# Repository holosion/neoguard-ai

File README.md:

# NeoGuard

NeoGuard is an offline-aware neonatal monitoring prototype for organizing clinical staff, patients, monitoring devices, vital-sign readings, alerts, and historical trends. It combines a React dashboard, a FastAPI service, and PostgreSQL. A separate experimental AI package trains a research-only warning model.

> **Project status:** This is a development and research prototype, not a clinically validated medical device or a production-ready care system. The AI model is trained on simulated data and is not clinically validated. Thresholds are provisional and require qualified clinical review before any care use. Current ESP32-S3 firmware uses the tested ST7789 screen, sensors, DS1302 clock, RGB/buzzer and SD logging. Wi-Fi provisioning and queued HTTPS synchronization are enabled after offline integration checks. See the firmware's current validation report for the actual hardware checks and limits.

## What the project does

- Provides sign-in for administrators, clinicians, and nurses, with role-aware and clinic-scoped access.
- Lets authorized staff manage patients, devices, monitoring sessions, alerts, and configured vital-sign thresholds.
- Accepts authenticated device sync batches and stores time-stamped readings and device telemetry in PostgreSQL.
- Uses stored readings to serve patient history and trend charts; dashboard values come from the API rather than a frontend sample-data mode.
- Tracks data freshness so staff can distinguish current readings from stale or missing data.
- Supports offline-safe sync: device event identifiers make retries idempotent, and readings retain their original session assignment.
- Optionally stores experimental model score snapshots separately from measured readings and deterministic threshold alerts.
- Keeps imported archive/training data in separate review tables instead of creating live patients or clinical readings.

## Repository map

```text
NeoGuard/
├── README.md                    # Project overview and setup (this file)
├── start-local.ps1              # Optional Windows launcher
├── LOCAL-RUN.md                 # Short local startup reference
├── backend/
│   ├── app/                     # FastAPI routes, auth, models, schemas, services
│   ├── migrations/              # Alembic database schema history
│   ├── scripts/                 # Admin bootstrap, smoke check, archive import
│   ├── tests/                   # API and PostgreSQL integration tests
│   ├── .env.example             # Backend configuration template
│   └── requirements*.txt        # Python dependencies
├── Frontend/
│   ├── src/                     # React pages, API clients, charts and components
│   ├── package.json             # Frontend scripts and dependencies
│   └── .env.example             # Frontend API configuration template
├── ai/
│   ├── train.py                 # Synthetic prototype training pipeline
│   ├── artifacts/               # Saved model artifact used by the API
│   ├── reports/                  # Training and archive audit reports
│   └── tests/                    # AI feature/model tests
├── akena firmware/akena_firmware/ # Current ESP32-S3 ST7789 firmware and setup guide
└── firmware/tests/              # Host-side measurement checks
```

## System architecture and data flow

```mermaid
flowchart LR
    Staff[Admin / clinician / nurse] --> UI[React dashboard]
    UI -->|REST requests, /api/v1| API[FastAPI]
    Device[Monitoring device] -->|Device-authenticated sync batch| API
    API -->|SQLAlchemy| DB[(PostgreSQL)]
    API -->|Patient history / overview / alerts| UI
    API -->|Optional experimental inference| Model[AI model artifact]
    API -->|Persist score snapshot separately| DB
```

The frontend calls the backend through `/api/v1`. In local development, Vite proxies API requests to FastAPI. Devices submit readings to the device sync endpoint using a provisioned device credential. The backend validates each item, stores accepted data and generated threshold alerts, and returns per-item results. Patient history and dashboard trends are then queried from PostgreSQL through the API.

The reading's `measured_at` timestamp is distinct from the server's `received_at` timestamp. This preserves when a measurement was taken even if a device uploads it later. A reading is associated with the monitoring session it originally belonged to, including when an offline device uploads after that session has ended. Device event IDs prevent duplicate readings on retry.

There is no frontend mock-data mode. A newly configured database can therefore show empty states until staff create records and a device or an authorized integration sends real readings. The current [device firmware](akena%20firmware/akena_firmware/README.md) reads sensors, drives the ST7789 screen and logs to SD. The network-enabled build reconnects to saved Wi-Fi settings and queues available readings after device/session provisioning. Live estimates carry poor quality until the full stability checks pass; the hosted bench view labels them accordingly.

## Technology

| Area | Current implementation |
|---|---|
| Frontend | React 18, Vite, React Router, Zustand, Recharts, Tailwind CSS |
| Backend | Python, FastAPI, Pydantic Settings, synchronous SQLAlchemy 2 |
| Database | PostgreSQL, managed through Alembic migrations |
| Staff security | JWT bearer access tokens, Argon2 password hashes, role and clinic access checks |
| Device security | Per-device random credential; the API stores a hash and supports credential rotation |
| AI prototype | Scikit-learn synthetic-data training pipeline and a JSON model artifact |
| Local orchestration | FastAPI development startup checks PostgreSQL and launches Vite if it is not already running |

## Start the project locally (Windows)

### Requirements

- Python and Node.js versions compatible with the dependencies in `backend/requirements.txt` and `Frontend/package-lock.json`.
- PostgreSQL installed and available locally, or the bundled local PostgreSQL runtime/data directory if your workspace provides it.
- PowerShell for the commands below and the optional `start-local.ps1` script.

### First-time setup

Run these commands from the repository root in PowerShell:

```powershell
py -m venv backend/.venv
backend/.venv/Scripts/python.exe -m pip install -r backend/requirements-dev.txt

Copy-Item backend/.env.example backend/.env
Copy-Item Frontend/.env.example Frontend/.env

Push-Location Frontend
npm ci
Pop-Location
```

Edit `backend/.env` and set:

- `DATABASE_URL` to the PostgreSQL database and credentials for this project.
- `JWT_SECRET_KEY` to a unique random secret of at least 32 characters. For example, generate one with `py -c "import secrets; print(secrets.token_urlsafe(48))"` and paste the output into the ignored `.env` file.
- `BOOTSTRAP_ADMIN_USERNAME` and `BOOTSTRAP_ADMIN_EMAIL` if you want different initial admin identifiers. Leave `BOOTSTRAP_ADMIN_PASSWORD` empty to enter the password interactively when creating the account.

Never commit `.env` files or share their secrets. The repository's `.gitignore` excludes them.

Create the PostgreSQL role and database if they do not already exist. For example, in a PostgreSQL shell as a database administrator:

```sql
CREATE ROLE neoguard LOGIN PASSWORD 'choose-a-local-password';
CREATE DATABASE neoguard OWNER neoguard;
```

Make `DATABASE_URL` use the same username, password, host, port, and database. Then run the migrations and create the initial admin account:

```powershell
Push-Location backend
.\.venv\Scripts\python.exe -m alembic upgrade head
.\.venv\Scripts\python.exe -m scripts.seed_admin
Pop-Location
```

The seed command creates the administrator and provisional threshold rows. It prompts for an admin password when `BOOTSTRAP_ADMIN_PASSWORD` is blank. It does not print or recover an existing admin password; reset credentials through an authorized operational process.

### Run the whole local application

From the repository root:

```powershell
Push-Location backend
..\.venv\Scripts\python.exe -m uvicorn app.main:app --host 127.0.0.1 --port 8000
```

In development mode, FastAPI checks that the configured PostgreSQL database accepts connections and starts Vite on port `5173` if the expected frontend is not already running. It can start a single installed PostgreSQL Windows service or the bundled local PostgreSQL runtime when available. Schema migrations remain a manual setup/upgrade step. Stop Uvicorn with `Ctrl+C`; it also stops the Vite process that it started. PostgreSQL remains running.

Open:

- Frontend: <http://127.0.0.1:5173>
- API health: <http://127.0.0.1:8000/health>
- Interactive API docs: <http://127.0.0.1:8000/docs> (disabled when `APP_ENV=production`)

Alternatively, run `./start-local.ps1` from the repository root after configuring the environment. The launcher checks dependencies and service readiness and prints the local URLs.

To run the frontend and backend separately, start the backend from `backend/` as above and run `npm run dev` from `Frontend/`. The Vite development server proxies `/api` requests to `http://127.0.0.1:8000`. For a separately hosted frontend, set `VITE_API_BASE_URL` in `Frontend/.env` and configure the deployed origin in backend `CORS_ORIGINS`.

## Main application areas

### Staff dashboard

- **Nurse and clinician views:** ward overview, patient list, patient details, vitals and trend history, active monitoring sessions, alerts, and device information.
- **Administrator views:** system overview, staff accounts and access requests, clinic configuration, device registry/health, sessions, and threshold settings.
- **Authentication:** username or email sign-in, forced password change for temporary credentials, and role-aware protected routes.
- Charts and KPI values are driven by API responses. Empty and stale states are shown when there are no recent readings.

### Backend API

The API prefix is `/api/v1`. The interactive OpenAPI documentation is available at `/docs` in development. Major endpoint groups include:

| Endpoint group | Purpose |
|---|---|
| `/auth` | Staff login, current user, password change, staff provisioning, access requests and administration |
| `/patients` | Patient records, risk profiles, reading history and experimental risk-score availability |
| `/devices` | Device registry, current device session, health/telemetry, secret rotation and device sync |
| `/sessions` | Start, list and stop patient/device monitoring assignments |
| `/alerts` | List/filter alerts and record staff acknowledgment |
| `/admin` | Administrative overview, clinic/user management and device health summaries |
| `/thresholds` | Read and configure rule-based alert thresholds |

Device ingestion uses `POST /api/v1/devices/sync`. Staff endpoints use staff bearer tokens; device sync uses the provisioned device bearer credential. The API validates value ranges, device/session ownership, timestamps, payload size, and duplicate event identifiers. Valid batch items receive accepted, duplicate, or rejected outcomes according to the sync contract.

### Database

PostgreSQL is the source of truth. Alembic migrations define and upgrade the schema; SQLAlchemy models represent its entities. Major data areas include:

- Clinics and staff users, including roles, password lifecycle state, and token versions.
- Patients and clinician-maintained risk profiles.
- Devices, hashed device credentials, registered components, telemetry, and component health.
- Monitoring sessions that link a clinic, patient, and device with database-enforced active-session constraints.
- Time-stamped readings and threshold alerts, including alert acknowledgment records.
- Versioned threshold configuration and audit records.
- Model registry and experimental risk-score snapshots.
- Separate archive import and research dataset tables for review-only data.

Run `alembic upgrade head` from `backend/` whenever pulling a schema migration. Do not use `Base.metadata.create_all()` as a substitute for migrations.

### AI and research data

The `ai/` package generates simulated monitoring sessions, trains an exploratory warning model, and writes a model artifact and reports. The API can load this artifact when `AI_MODE=prototype`; set `AI_MODE=disabled` to turn off model scoring. Threshold-based alerts operate independently of model availability. Model outputs are marked as synthetic research estimates and are not diagnoses or validated clinical probabilities.

The archive audit/import path stages de-identified research records in separate dataset tables for review. It does not insert imported subjects into the live patient table or turn archive rows into clinical readings. Review `ai/README.md` and `backend/docs/archive-data-storage.md` for model and archive details.

## Security and operational notes

- Staff passwords are stored as hashes, and JWT secrets must be unique and private.
- Temporary staff passwords require a password change and expire; password changes/reset invalidate existing access tokens.
- Device credentials are generated per device, stored as hashes, and can be rotated. A newly provisioned device secret is returned once; save it securely.
- Non-admin staff access is scoped to their clinic. Use the least privileged role needed.
- Do not put real patient identifiers or clinical data in commits, screenshots, test fixtures, or training reports.
- Configure explicit production `CORS_ORIGINS`; wildcard origins and localhost origins are rejected for production settings.
- Apply TLS, backups, access review, retention rules, monitoring, and deployment-specific secret management before any deployment beyond local development.
- Provisional threshold defaults require clinical review and approval before being used for care decisions.

## Development and verification

Install backend development dependencies with `backend/requirements-dev.txt` and frontend dependencies with `npm ci` in `Frontend/`.

Useful commands from the repository root:

```powershell
# Backend contract and PostgreSQL-backed API smoke flow (requires configured DB and migrations)
Push-Location backend
.\.venv\Scripts\python.exe -m scripts.smoke_test_live
Pop-Location

# Frontend production build
Push-Location Frontend
npm run build
Pop-Location

# Python and AI unit tests
backend/.venv/Scripts/python.exe -m pytest -q
```

PostgreSQL integration tests require `NEOGUARD_TEST_DATABASE_URL` to point to a dedicated test database. Use a disposable database; the tests create and clean up their own test schema. Do not point integration tests at a database containing project or patient records.

The live smoke script exercises the configured API and PostgreSQL flow, including authentication/access controls, patient/device/session creation, device sync and deduplication, stored history, alerts, and device health; it cleans up the temporary records it creates. Read its output before using it against any shared environment.

## Current limits and next integration boundary

- `akena firmware/akena_firmware/` is the current ST7789 firmware. Its default build combines local monitoring with Wi-Fi setup and queued backend synchronization; an offline build option remains available. See its README and validation report.
- The database and API can store device-submitted vitals and serve historical trends, but an actual monitoring device or another trusted producer must send those readings.
- The AI model uses simulated data and has no clinical validation. Archive data is staged for review and is not clinical ground truth.
- This repository is not a replacement for clinical judgment, a validated alarm system, or a regulated medical device.

## Additional documentation

- [Local run notes](LOCAL-RUN.md)
- [AI prototype and reproducibility](ai/README.md)
- [Research archive storage notes](backend/docs/archive-data-storage.md)
- [MIT License](LICENSE)

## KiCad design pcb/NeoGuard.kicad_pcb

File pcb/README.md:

# Akena NeoGuard — SPI display revision D

Updated 29 October 2026. Open `NeoGuard.kicad_pro` in KiCad 10 or read `NeoGuard-schematic.pdf`.

The display is the ST7789 240×280 SPI screen, called OLED in earlier project notes and identified by the current firmware and hardware-test records. This design follows that interface.

## Changes

- Removed the 16×2 LCD, AHCT245 buffer, contrast trimmer and LCD backlight circuitry.
- Restored the eight-signal SPI display cable and optional backlight jumper.
- Exposed all 36 GPIO identities in the DevKitC-style external GPIO set plus 3V3, GND, EN and 5V. Every used pin connects through a wire and named net. Twenty unused external connections have no-connect X marks.
- GPIO13 and carrier J1 pin22 are unconnected. Leave J1 pin22 disconnected.
- Preserved the previous LCD project in `.history/pre-spi-d-20261029`.

## Display wiring

| J5 pin | Display signal | Connection |
|---|---|---|
| 1 | GND | Common ground |
| 2 | VCC | Selected V3V3 |
| 3 | SCK / SCL | GPIO12 |
| 4 | MOSI / SDA | GPIO11 |
| 5 | RST / RES | GPIO8 |
| 6 | DC | GPIO9 |
| 7 | CS | GPIO10 |
| 8 | BL / BLK | JP4 optional 3V3 backlight supply |

Screen SDA/SCL are SPI signals. Sensor I2C remains SDA=GPIO4, SCL=GPIO5. JP4 is normally open/DNP; fit only for a verified 3.3V-compatible backlight input with suitable current limiting. Firmware has no backlight GPIO.

RTC CLK/DAT/CE remain GPIO6/7/14. SD CS/SCK/MOSI/MISO remain GPIO21/40/41/42. Buzzer remains GPIO15 and RGB remains GPIO16/17/18.

## Controller and mechanical interface

U1 represents the offboard development board using logical GPIO identities, not physical pin positions. Duplicate supply/ground contacts are represented by common logical supply pins. X means no external carrier connection; EN, USB, strapping and memory circuitry retain their functions on the development board. GPIO26–34 are not external carrier interfaces. GPIO35–37 are unused and may be reserved by memory on some variants.

J1 is a 2×12 cable header, not a development-board socket. J5 is a 1×8 functional cable header, not a mechanically matched screen footprint. Assemble cables by signal name using Connections.csv. Exact controller model, module pin order and mounting dimensions still require confirmation.

## Power and assembly

All grounds join. No onboard regulator or reverse-polarity protection. J9 accepts regulated 3V3/GND/5V on pins1/2/3. External 5V is only needed if the SD or buzzer requires it; the display uses 3V3.

- JP1: one shunt; pins1–2 selects DEV3V3, pins2–3 selects EXT3V3. Never bridge both sources.
- JP2: pins1–2 selects 3V3 SD supply; pins2–3 selects 5V. Signals must remain 3.3V compatible.
- JP3: pins1–2 selects 3V3 buzzer supply; pins2–3 selects 5V.
- R1/R2: optional 4.7k I2C pull-ups to 3V3, normally DNP when fitted on modules.
- Q1: PN2222A E1/B2/C3; verify purchased pinout. R6=1k, R7=10k pulldown, D1 cathode to buzzer positive. Buzzer load assumption: at most 20mA.

Power controller and modules together. Verify regulator current capacity. Sensor breakouts must support 3.3V supply and I2C. RTC battery charging remains disabled in firmware.

## Files and regeneration

The root schematic uses NeoGuard-display.kicad_sch and NeoGuard-power.kicad_sch. Keep these with the local library and project. BOM.csv, Connections.csv, Controller-pins.csv, ERC.json, DRC.json and verification_summary.json describe this revision. Akena-SPI-PCB-project.zip is the portable review package.

Run build_schematic.py; export the KiCad XML netlist to NeoGuard.net.xml; run build_pcb.py and finish_board.py using KiCad Python; run verify_design.py, ERC and DRC with schematic parity. Export PDF and previews after changes. route_spi.py is the routing helper. The migration script is retained only in the history folder.

Checks establish connectivity and configured-rule compliance, not purchased-module fit, assembled operation or clinical suitability. See VALIDATION.md for results.

Controller reference: https://documentation.espressif.com/esp-dev-kits/en/latest/esp32s3/esp32-s3-devkitc-1/user_guide_v1.1.html
Firmware wiring: ../akena firmware/akena_firmware/README.md

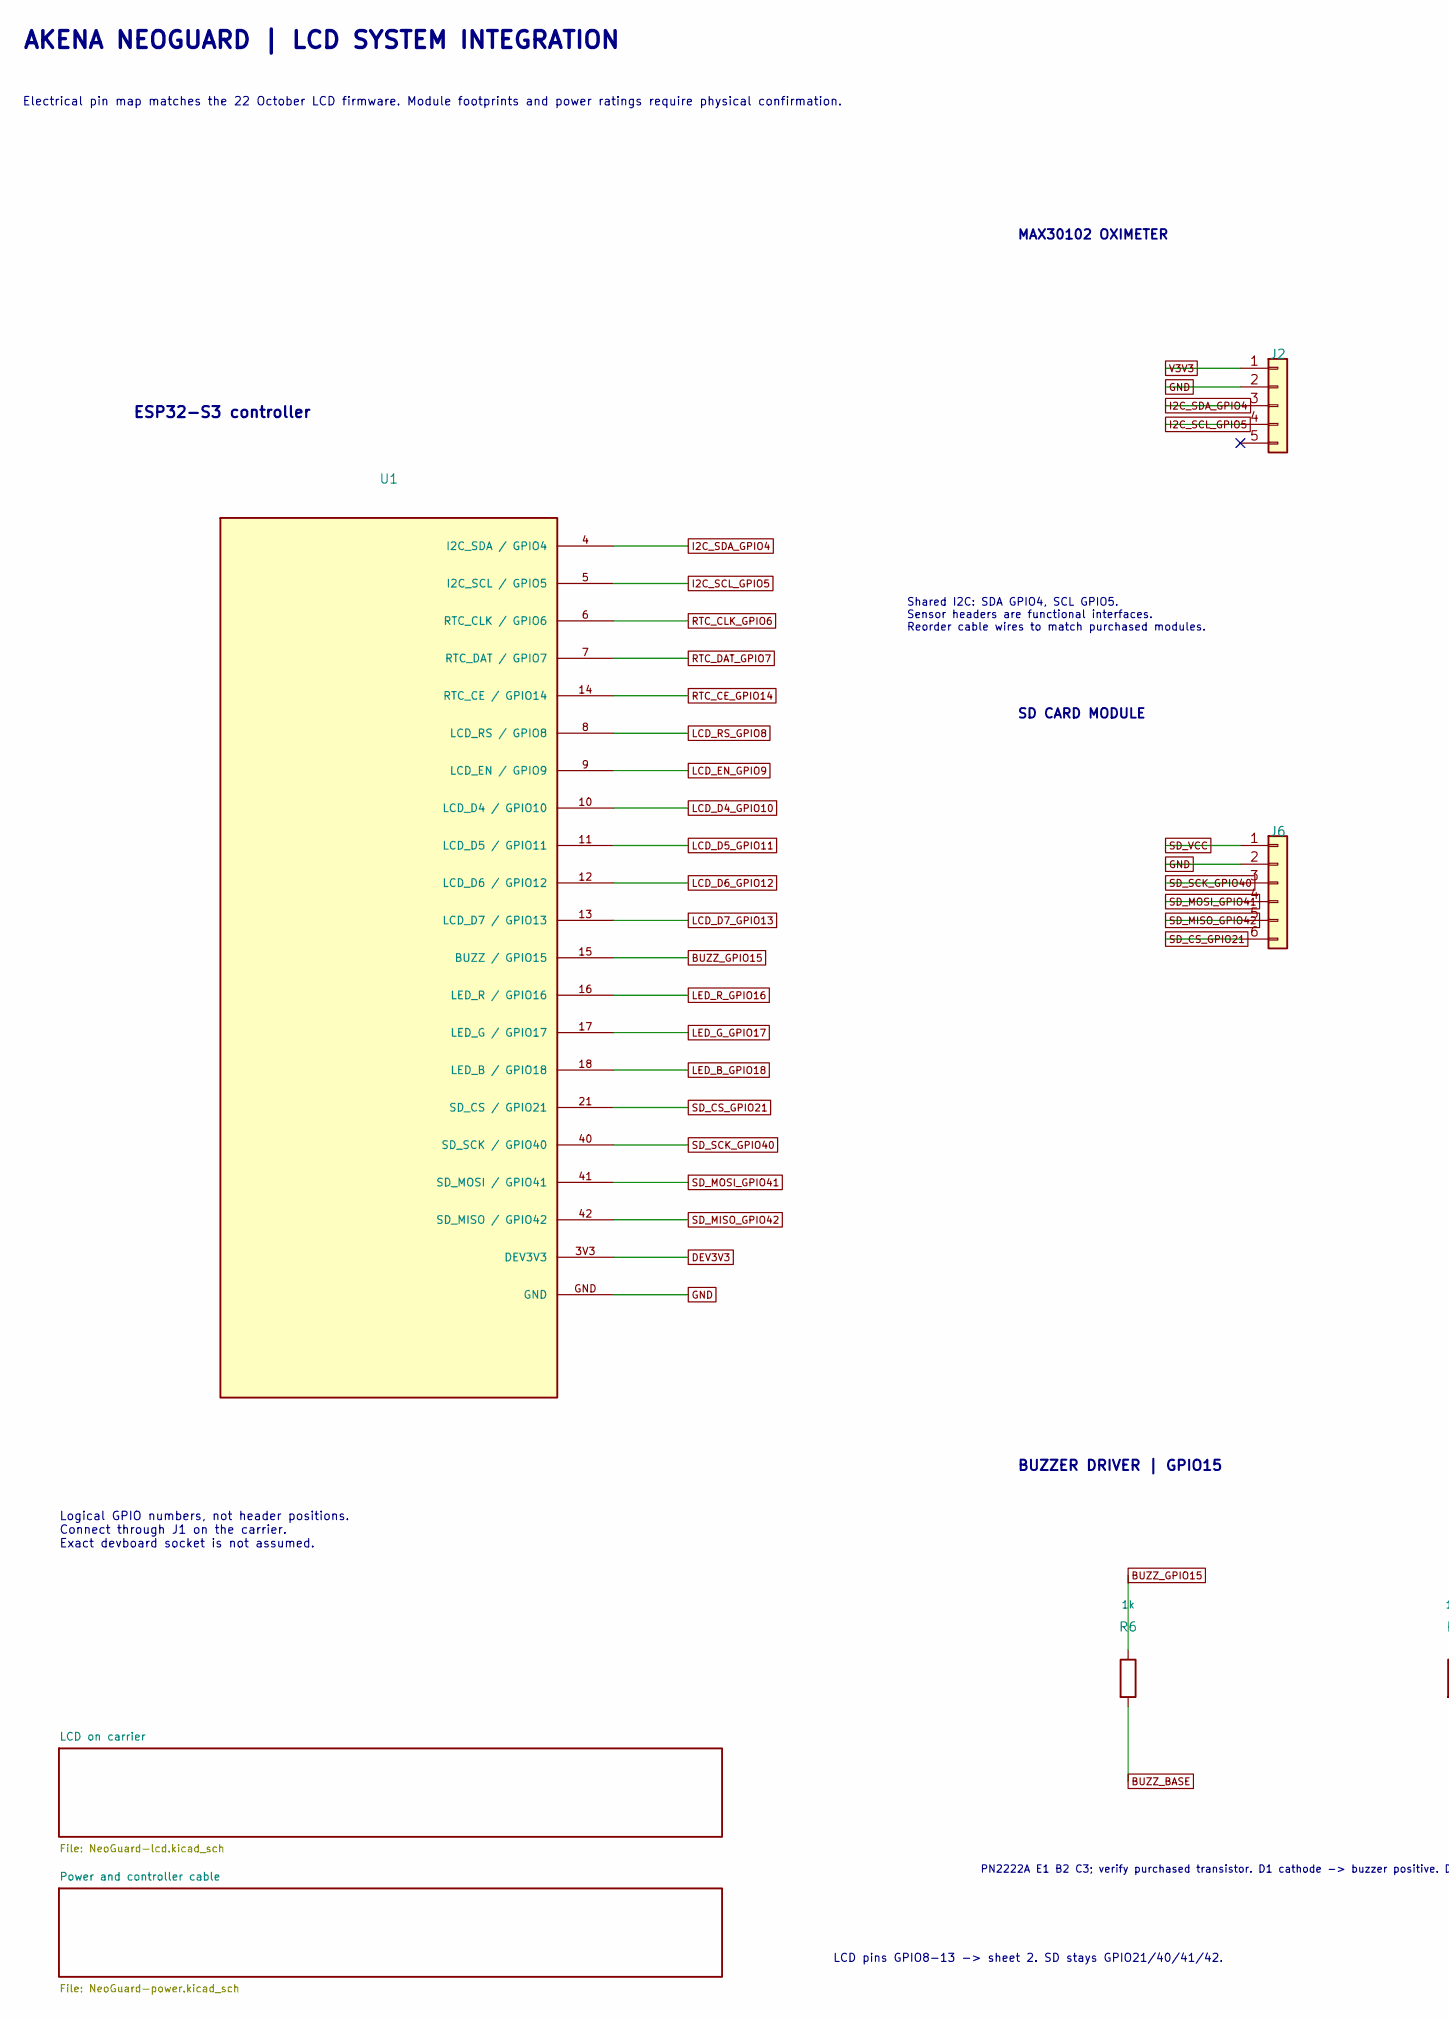
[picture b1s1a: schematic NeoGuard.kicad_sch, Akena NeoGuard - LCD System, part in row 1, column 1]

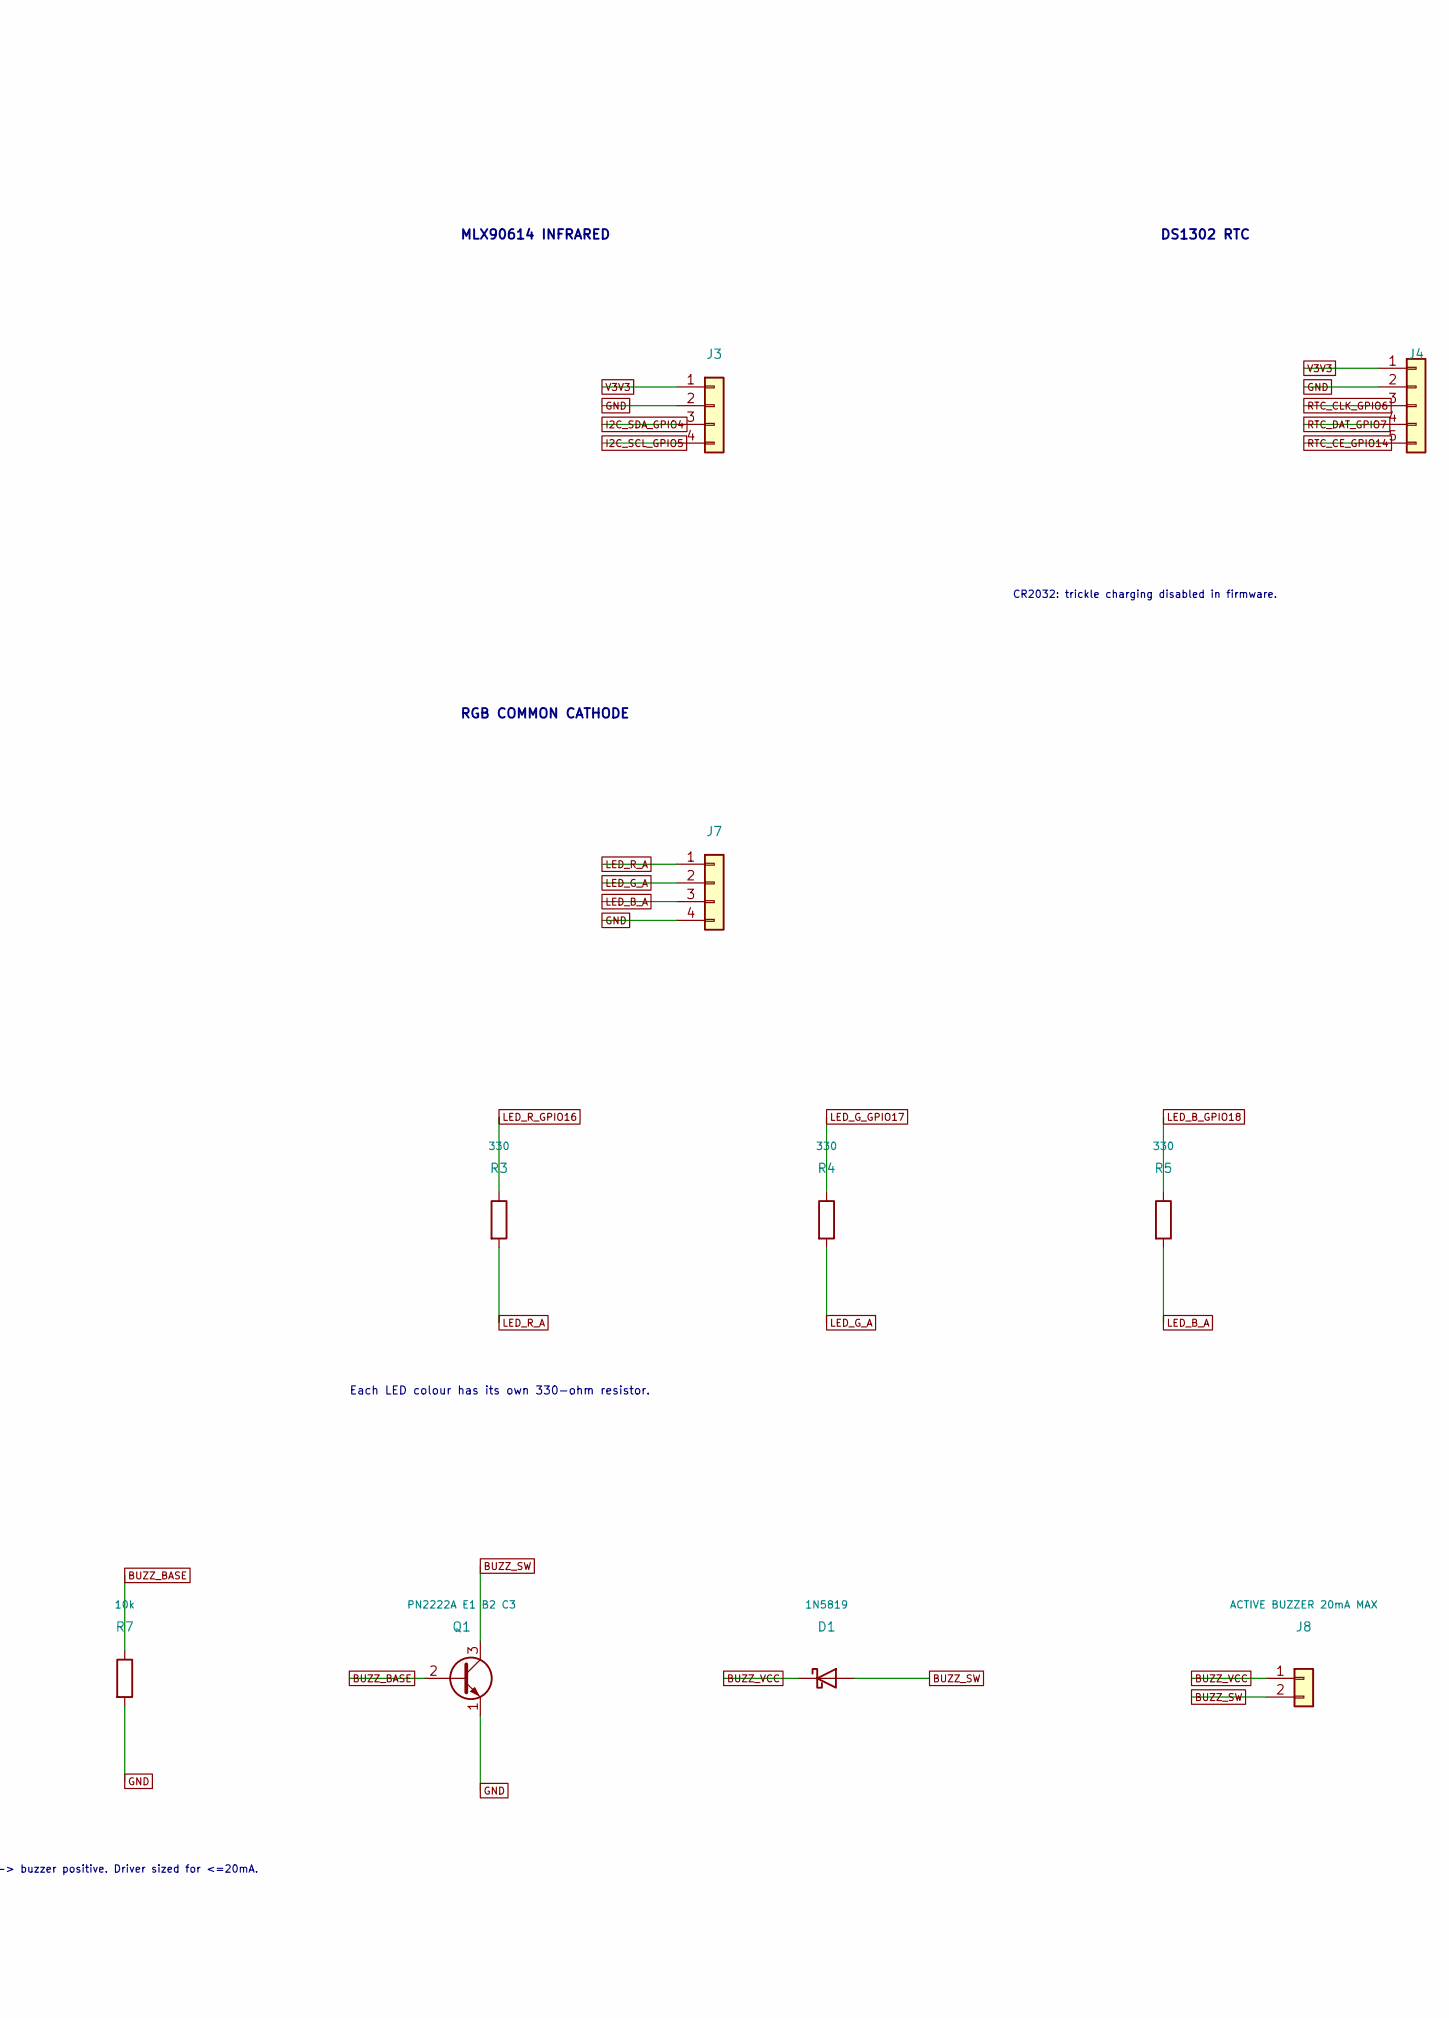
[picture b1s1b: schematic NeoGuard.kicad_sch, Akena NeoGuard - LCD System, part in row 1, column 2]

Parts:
D1: 1N5819; D_DO-41_SOD81_P10.16mm_Horizontal
J2: MAX30102 BREAKOUT; PinHeader_1x05_P2.54mm_Vertical
J3: MLX90614 3V3 BREAKOUT; PinHeader_1x04_P2.54mm_Vertical
J4: DS1302 MODULE; PinHeader_1x05_P2.54mm_Vertical
J6: SPI MICROSD MODULE; PinHeader_1x06_P2.54mm_Vertical
J7: EXTERNAL RGB COMMON CATHODE; PinHeader_1x04_P2.54mm_Vertical
J8: ACTIVE BUZZER 20mA MAX; PinHeader_1x02_P2.54mm_Vertical
Q1: PN2222A E1 B2 C3; TO-92_Inline_Wide
R3, R4, R5: 330; R_Axial_DIN0207_L6.3mm_D2.5mm_P10.16mm_Horizontal
R6: 1k; R_Axial_DIN0207_L6.3mm_D2.5mm_P10.16mm_Horizontal
R7: 10k; R_Axial_DIN0207_L6.3mm_D2.5mm_P10.16mm_Horizontal
U1: ESP32-S3 DEVELOPMENT BOARD

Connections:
BUZZ_BASE: Q1.2 (B), R6.2, R7.1
BUZZ_GPIO15: R6.1, U1.15 (BUZZ / GPIO15); also elsewhere on the board
BUZZ_SW: D1.2 (A), J8.2, Q1.3 (C)
BUZZ_VCC: D1.1 (K), J8.1; also elsewhere on the board
GND: J2.2, J3.2, J4.2, J6.2, J7.4, Q1.1 (E), R7.2, U1.GND; also elsewhere on the board
I2C_SCL_GPIO5: J2.4, J3.4, U1.5 (I2C_SCL / GPIO5); also elsewhere on the board
I2C_SDA_GPIO4: J2.3, J3.3, U1.4 (I2C_SDA / GPIO4); also elsewhere on the board
LED_B_A: J7.3, R5.2
LED_B_GPIO18: R5.1, U1.18 (LED_B / GPIO18); also elsewhere on the board
LED_G_A: J7.2, R4.2
LED_G_GPIO17: R4.1, U1.17 (LED_G / GPIO17); also elsewhere on the board
LED_R_A: J7.1, R3.2
LED_R_GPIO16: R3.1, U1.16 (LED_R / GPIO16); also elsewhere on the board
RTC_CE_GPIO14: J4.5, U1.14 (RTC_CE / GPIO14); also elsewhere on the board
RTC_CLK_GPIO6: J4.3, U1.6 (RTC_CLK / GPIO6); also elsewhere on the board
RTC_DAT_GPIO7: J4.4, U1.7 (RTC_DAT / GPIO7); also elsewhere on the board
SD_CS_GPIO21: J6.6, U1.21 (SD_CS / GPIO21); also elsewhere on the board
SD_MISO_GPIO42: J6.5, U1.42 (SD_MISO / GPIO42); also elsewhere on the board
SD_MOSI_GPIO41: J6.4, U1.41 (SD_MOSI / GPIO41); also elsewhere on the board
SD_SCK_GPIO40: J6.3, U1.40 (SD_SCK / GPIO40); also elsewhere on the board
SD_VCC: J6.1; also elsewhere on the board
V3V3: J2.1, J3.1, J4.1; also elsewhere on the board

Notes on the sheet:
AKENA NEOGUARD | LCD SYSTEM INTEGRATION
Electrical pin map matches the 22 October LCD firmware. Module footprints and power ratings require physical confirmation.
ESP32-S3 controller
Logical GPIO numbers, not header positions. Connect through J1 on the carrier. Exact devboard socket is not assumed.
MAX30102 OXIMETER
MLX90614 INFRARED
DS1302 RTC
SD CARD MODULE
RGB COMMON CATHODE
Shared I2C: SDA GPIO4, SCL GPIO5. Sensor headers are functional interfaces. Reorder cable wires to match purchased modules.
CR2032: trickle charging disabled in firmware.
Each LED colour has its own 330-ohm resistor.
BUZZER DRIVER | GPIO15
PN2222A E1 B2 C3; verify purchased transistor. D1 cathode -> buzzer positive. Driver sized for <=20mA.
LCD pins GPIO8-13 -> sheet 2. SD stays GPIO21/40/41/42.

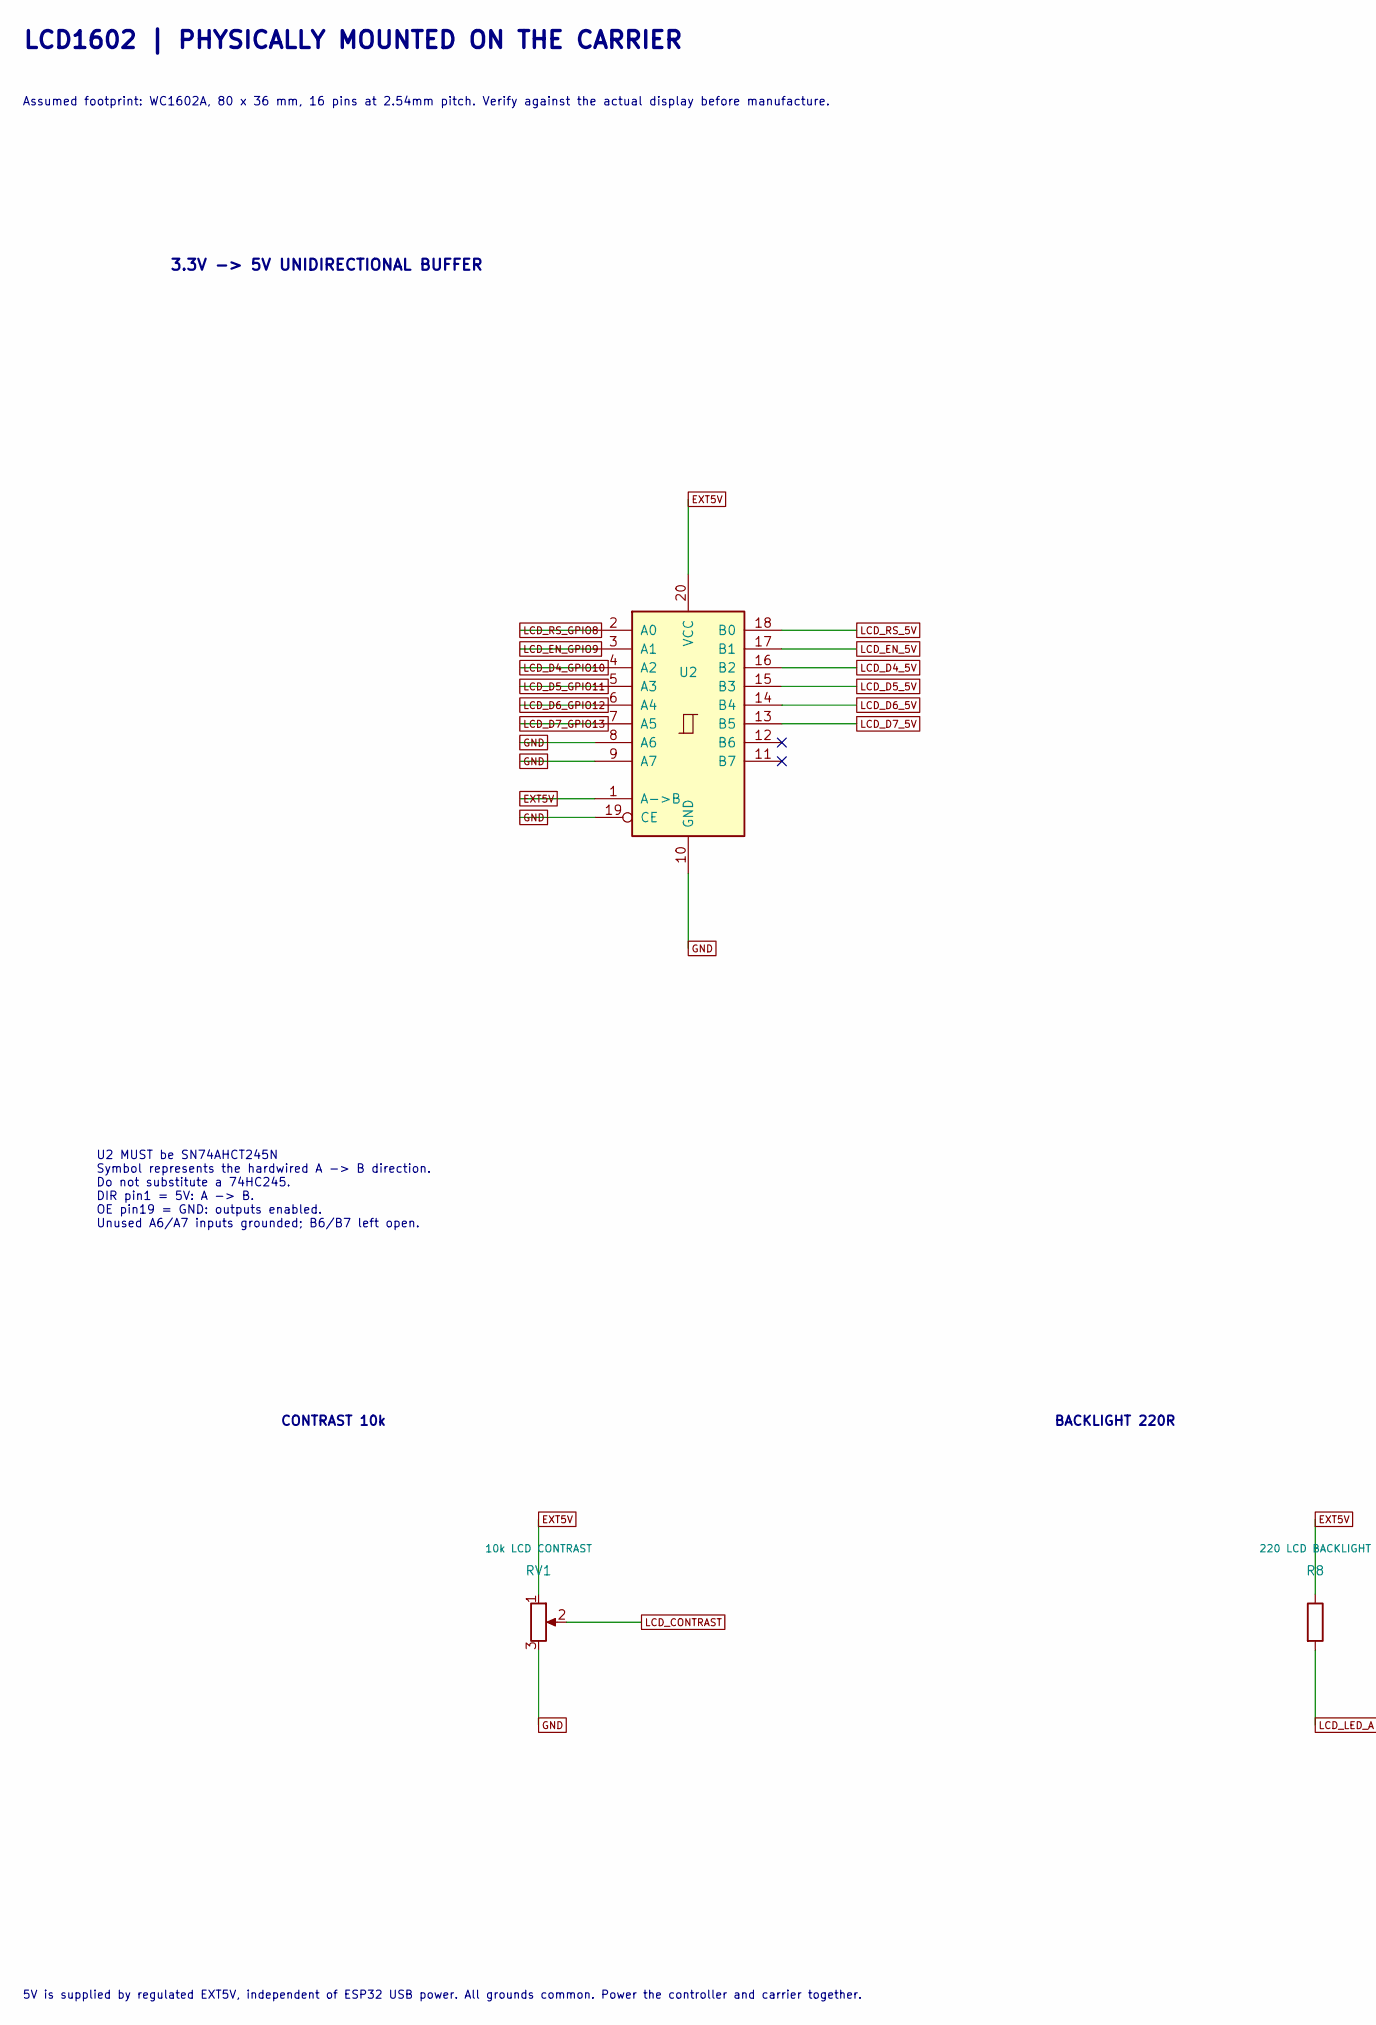
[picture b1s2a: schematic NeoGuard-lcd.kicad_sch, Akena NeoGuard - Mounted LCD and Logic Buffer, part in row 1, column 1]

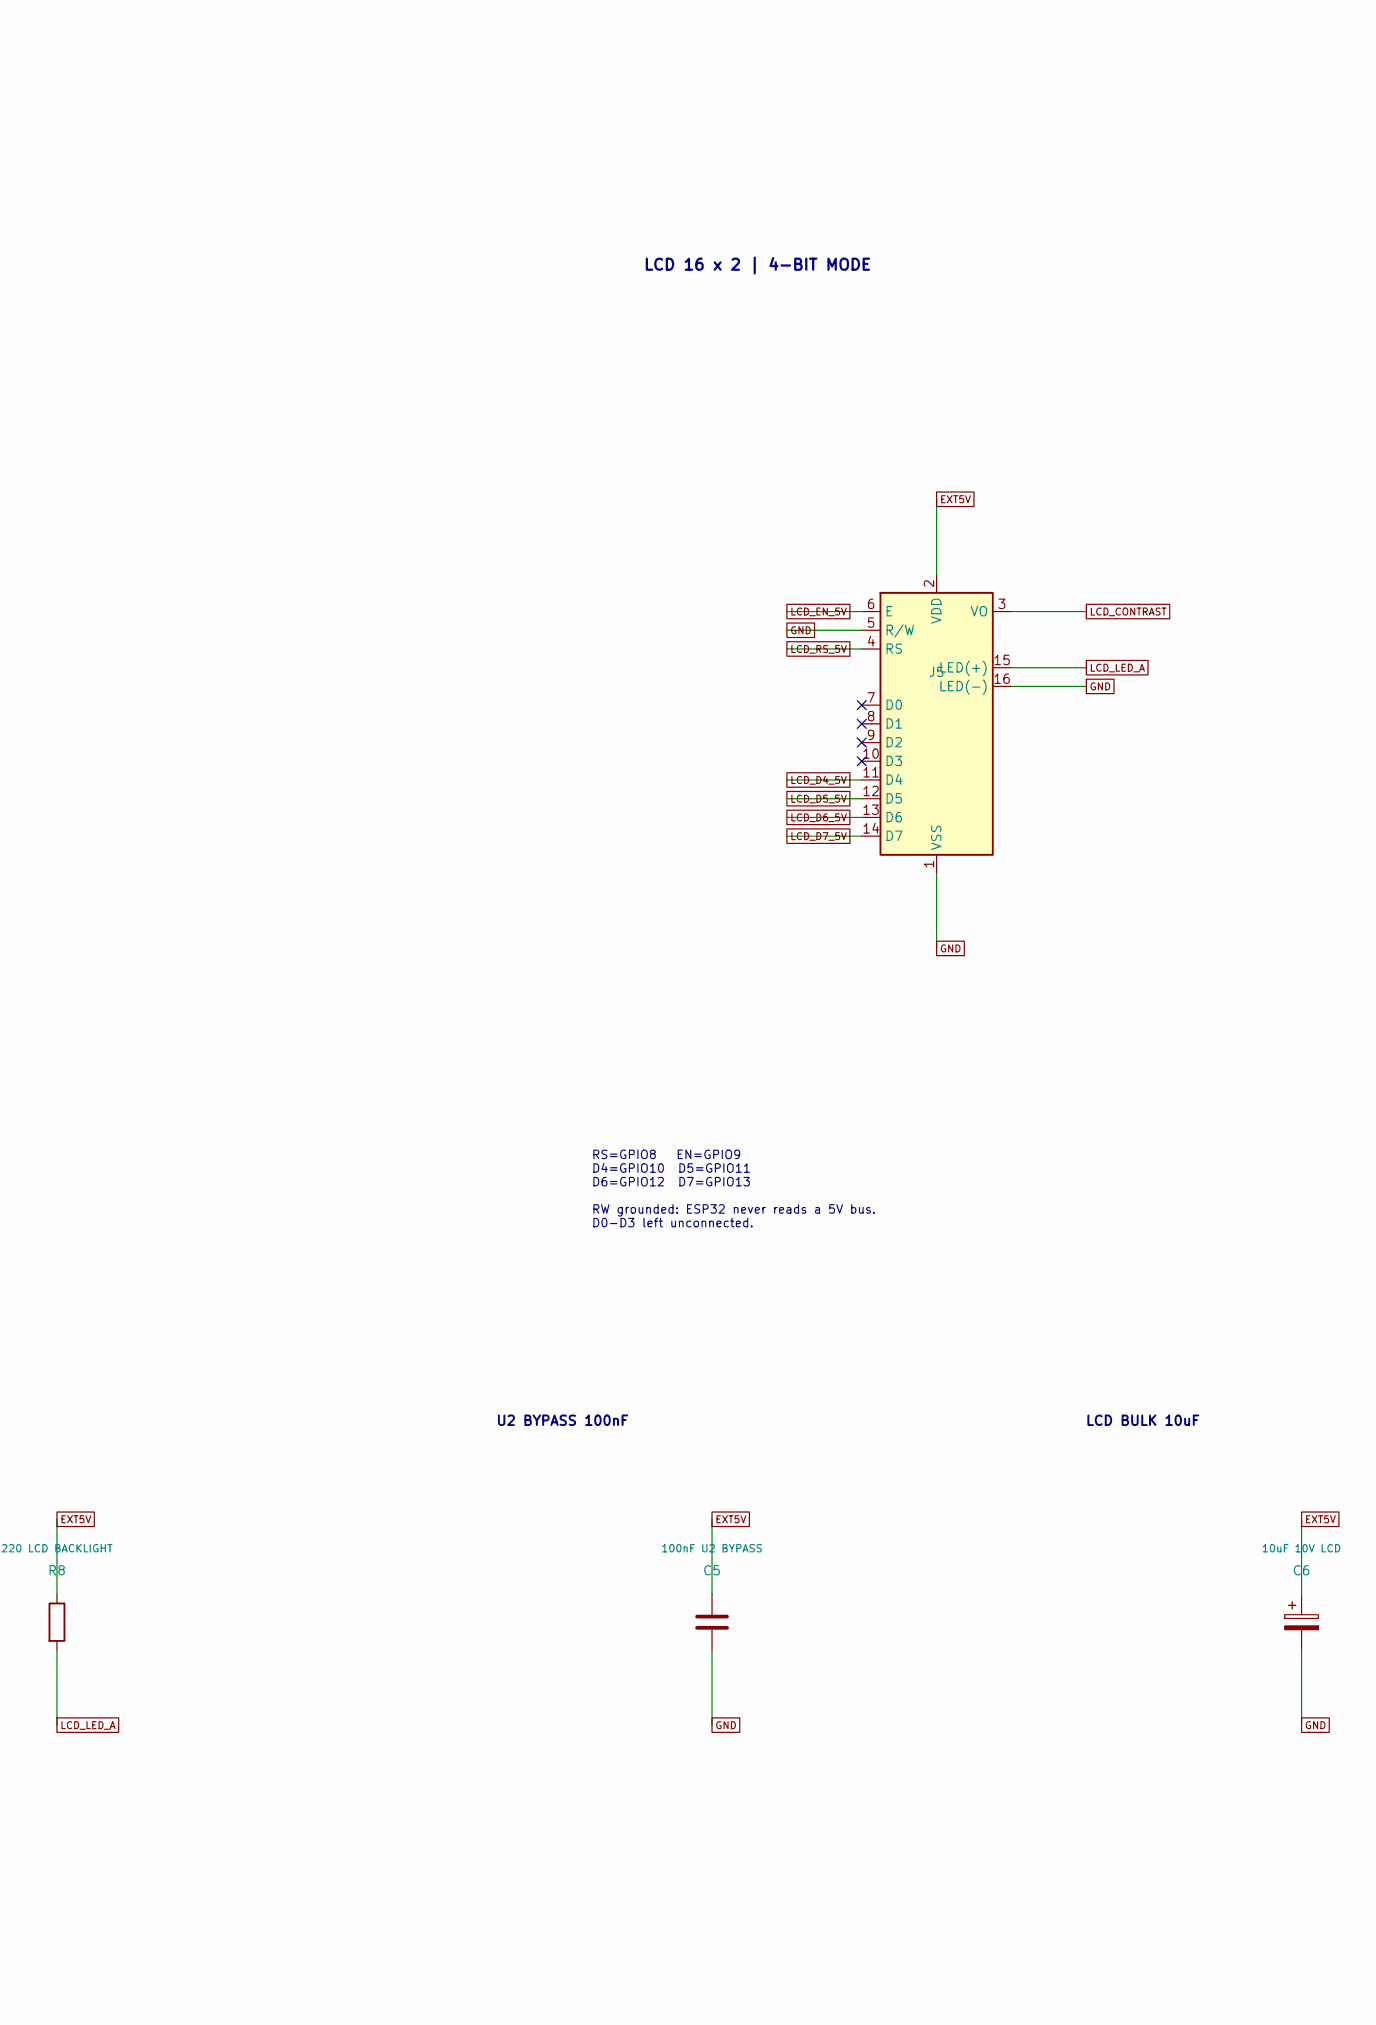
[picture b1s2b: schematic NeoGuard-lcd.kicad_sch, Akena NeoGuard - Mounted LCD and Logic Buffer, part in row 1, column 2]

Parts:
C5: 100nF U2 BYPASS; C_Disc_D5.0mm_W2.5mm_P5.00mm
C6: 10uF 10V LCD; CP_Radial_D6.3mm_P2.50mm
J5: WC1602A LCD 16x2 - VERIFY ACTUAL MODULE; LCD1602_80x36_Mounting
R8: 220 LCD BACKLIGHT; R_Axial_DIN0207_L6.3mm_D2.5mm_P10.16mm_Horizontal
RV1: 10k LCD CONTRAST; Potentiometer_Bourns_3296W_Vertical
U2: SN74AHCT245N - NOT 74HC245; DIP-20_W7.62mm

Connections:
EXT5V: C5.1, C6.1, J5.2 (VDD), R8.1, RV1.1, U2.1 (A->B), U2.20 (VCC); also elsewhere on the board
GND: C5.2, C6.2, J5.1 (VSS), J5.5 (R/W), J5.16 (LED(-)), RV1.3, U2.8 (A6), U2.9 (A7), U2.10 (GND), U2.19 (CE); also elsewhere on the board
LCD_CONTRAST: J5.3 (VO), RV1.2
LCD_D4_5V: J5.11 (D4), U2.16 (B2)
LCD_D4_GPIO10: U2.4 (A2); also elsewhere on the board
LCD_D5_5V: J5.12 (D5), U2.15 (B3)
LCD_D5_GPIO11: U2.5 (A3); also elsewhere on the board
LCD_D6_5V: J5.13 (D6), U2.14 (B4)
LCD_D6_GPIO12: U2.6 (A4); also elsewhere on the board
LCD_D7_5V: J5.14 (D7), U2.13 (B5)
LCD_D7_GPIO13: U2.7 (A5); also elsewhere on the board
LCD_EN_5V: J5.6 (E), U2.17 (B1)
LCD_EN_GPIO9: U2.3 (A1); also elsewhere on the board
LCD_LED_A: J5.15 (LED(+)), R8.2
LCD_RS_5V: J5.4 (RS), U2.18 (B0)
LCD_RS_GPIO8: U2.2 (A0); also elsewhere on the board

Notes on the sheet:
LCD1602 | PHYSICALLY MOUNTED ON THE CARRIER
Assumed footprint: WC1602A, 80 x 36 mm, 16 pins at 2.54mm pitch. Verify against the actual display before manufacture.
3.3V -> 5V UNIDIRECTIONAL BUFFER
U2 MUST be SN74AHCT245N Symbol represents the hardwired A -> B direction. Do not substitute a 74HC245. DIR pin1 = 5V: A -> B. OE pin19 = GND: outputs enabled. Unused A6/A7 inputs grounded; B6/B7 left open.
LCD 16 x 2 | 4-BIT MODE
RS=GPIO8 EN=GPIO9 D4=GPIO10 D5=GPIO11 D6=GPIO12 D7=GPIO13 RW grounded: ESP32 never reads a 5V bus. D0-D3 left unconnected.
CONTRAST 10k
BACKLIGHT 220R
U2 BYPASS 100nF
LCD BULK 10uF
5V is supplied by regulated EXT5V, independent of ESP32 USB power. All grounds common. Power the controller and carrier together.
